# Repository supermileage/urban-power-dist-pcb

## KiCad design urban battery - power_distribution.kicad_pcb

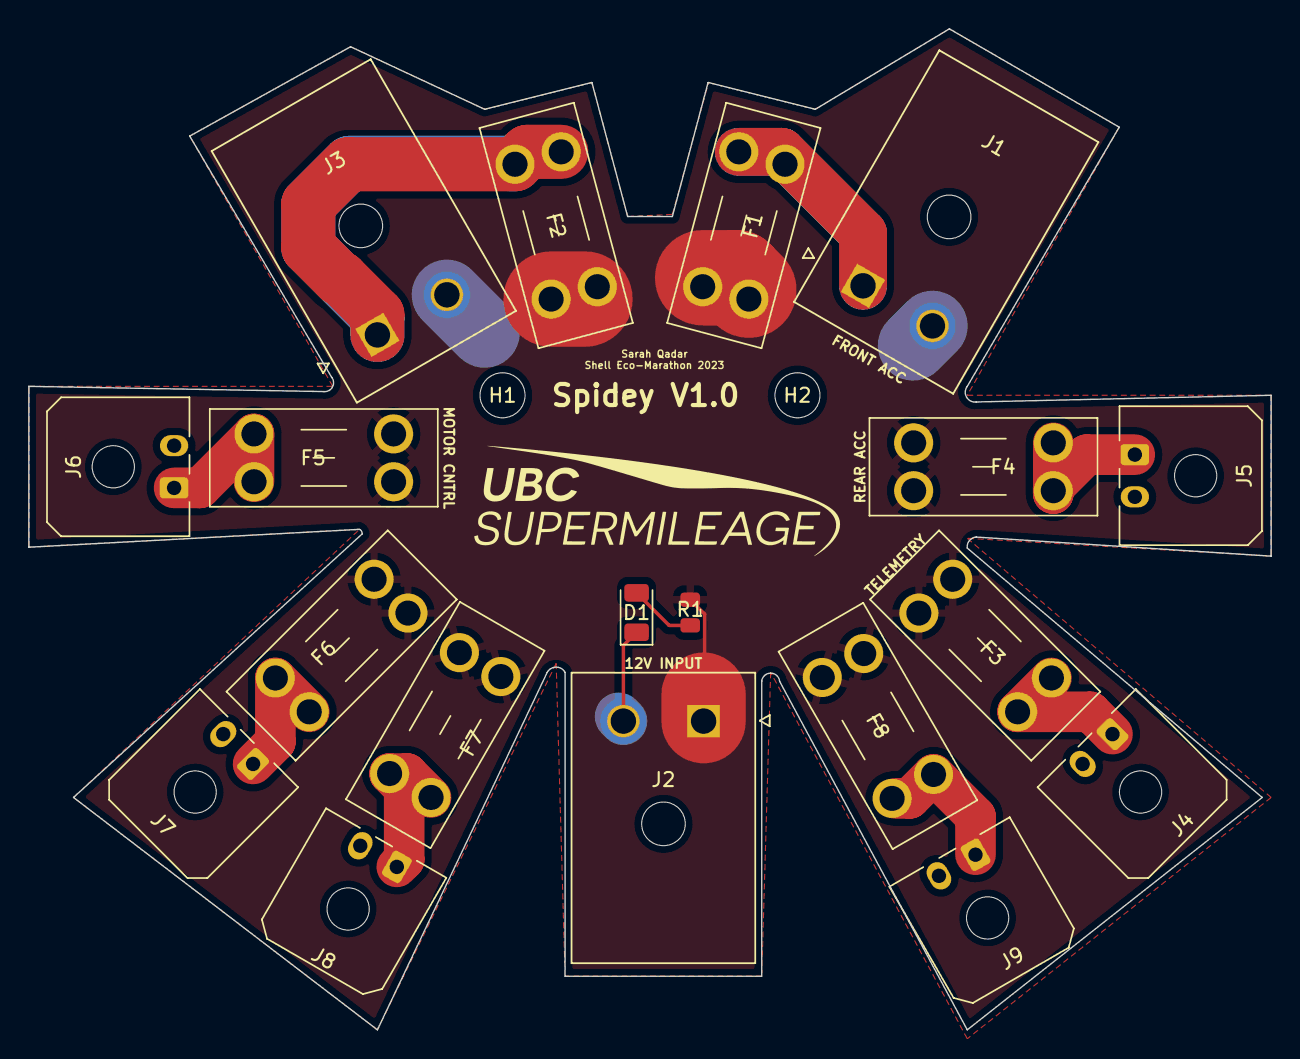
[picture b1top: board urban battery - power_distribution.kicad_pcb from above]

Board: 2 copper layers, 88.3 x 71.1 mm, 21 parts (0 on the bottom side), 10 nets.

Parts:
D1: LED; LED_1206_3216Metric
F1, F2, F3, F4, F5, F6, F7, F8: Fuse; Fuseholder_Blade_Mini_Keystone_3568
H1, H2: MountingHole; MountingHole_3.2mm_M3
J1: FRONT_ACC_OUT; MOLEX_2002411222
J2: 12V_IN; MOLEX_2002411222
J3: 12VHC_OUT_EXTRA; MOLEX_2002411222
J4: TEL_OUT; Molex_Micro-Fit_3.0_43650-0200_1x02_P3.00mm_Horizontal
J5: REAR ACC; Molex_Micro-Fit_3.0_43650-0200_1x02_P3.00mm_Horizontal
J6: MTR_CTRL_OUT; Molex_Micro-Fit_3.0_43650-0200_1x02_P3.00mm_Horizontal
J7, J8, J9: 12VLC_OUT_EXTRA; Molex_Micro-Fit_3.0_43650-0200_1x02_P3.00mm_Horizontal
R1: 487K; R_0805_2012Metric

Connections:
+12V: F1.1, F2.1, F3.1, F4.1, F5.1, F6.1, F7.1, F8.1, J2.1, R1.2
GND: D1.1 (K), F2.2, J1.2, J2.2, J3.1, J3.2, J4.2, J5.2, J6.2, J7.2, J8.2, J9.2
unnamed: D1.2 (A), R1.1
unnamed: F1.2, J1.1
unnamed: F3.2, J4.1
unnamed: F4.2, J5.1
unnamed: F5.2, J6.1
unnamed: F6.2, J7.1
unnamed: F7.2, J8.1
unnamed: F8.2, J9.1

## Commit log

2023-02-05 made readme
2023-02-07 schematic done. symbols added + connected, everything labeled
2023-02-07 Assigned footprints and datasheets to every component
2023-02-15 added shunt resistor in front of LED and did most of layout
2023-02-15 updated layout, added logo
2023-02-28 figuring out shape of board
2023-02-28 completed moat of layout including pcb shape, fill zones, traces, logo, name and component arrangement
2023-03-03 fixed issue od 12V input going through LED
2023-03-03 softened sharp inner corners of pcb
2023-03-04 pcb routing,added mounting holes and proper labels
2023-03-04 fixed schematic and layout bugs
2023-03-04 final layout touches
2023-03-05 generated gerbers and drill file
2023-03-06 fixed clearance issue addressed by DRC
2023-03-06 created gerbers
2023-03-06 generated drill files again and edited edge cuts + made logo silk screen
2023-03-06 again generated gerber file
